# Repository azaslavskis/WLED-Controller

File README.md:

# WLED Controller ⚡

A compact ESP32-C3 based controller board for running addressable LED strips with **WLED** and integrating them into **Home Assistant**.

---

## What this project includes

- **Hardware design files** (KiCad project, production outputs, 3D model assets)
- **Firmware patch helper** for building a patched WLED version
- **Assembly references** for the current controller revision

---

## ⚠️ Current hardware status

> **Do not order this PCB revision yet** — the board still has known issues.

### Known issues to fix before ordering

1. `R7` / `EN` pin of `XL1509-5.0V` should be connected to **GND**, not input.
2. ESP32-C3 **pin 9** must be pulled correctly for reliable boot.
3. `DS18B20` pin must be pulled to **3.3V** (fixed on rev **1.6**).
4. More physical spacing is needed for `C1`, `C3`, and `C9`.

---

## Assembled unit

---

## Build patched firmware

Run the helper script directly:

```bash
wget https://raw.githubusercontent.com/azaslavskis/WLED-Controller/refs/heads/main/software/WLED-Git_patch/patch.sh \
  && chmod +x patch.sh \
  && ./patch.sh
```

---

## Repository layout (high level)

- `hardware/` → PCB project, exports, and fabrication artifacts
- `software/` → firmware patching/build helper files
- `3d-models/` → enclosure and mounting models

---

## Project goal

Create a reliable, DIY-friendly LED controller that is easy to deploy in smart-home setups and flexible enough for custom lighting projects.

## Rework is comming soon

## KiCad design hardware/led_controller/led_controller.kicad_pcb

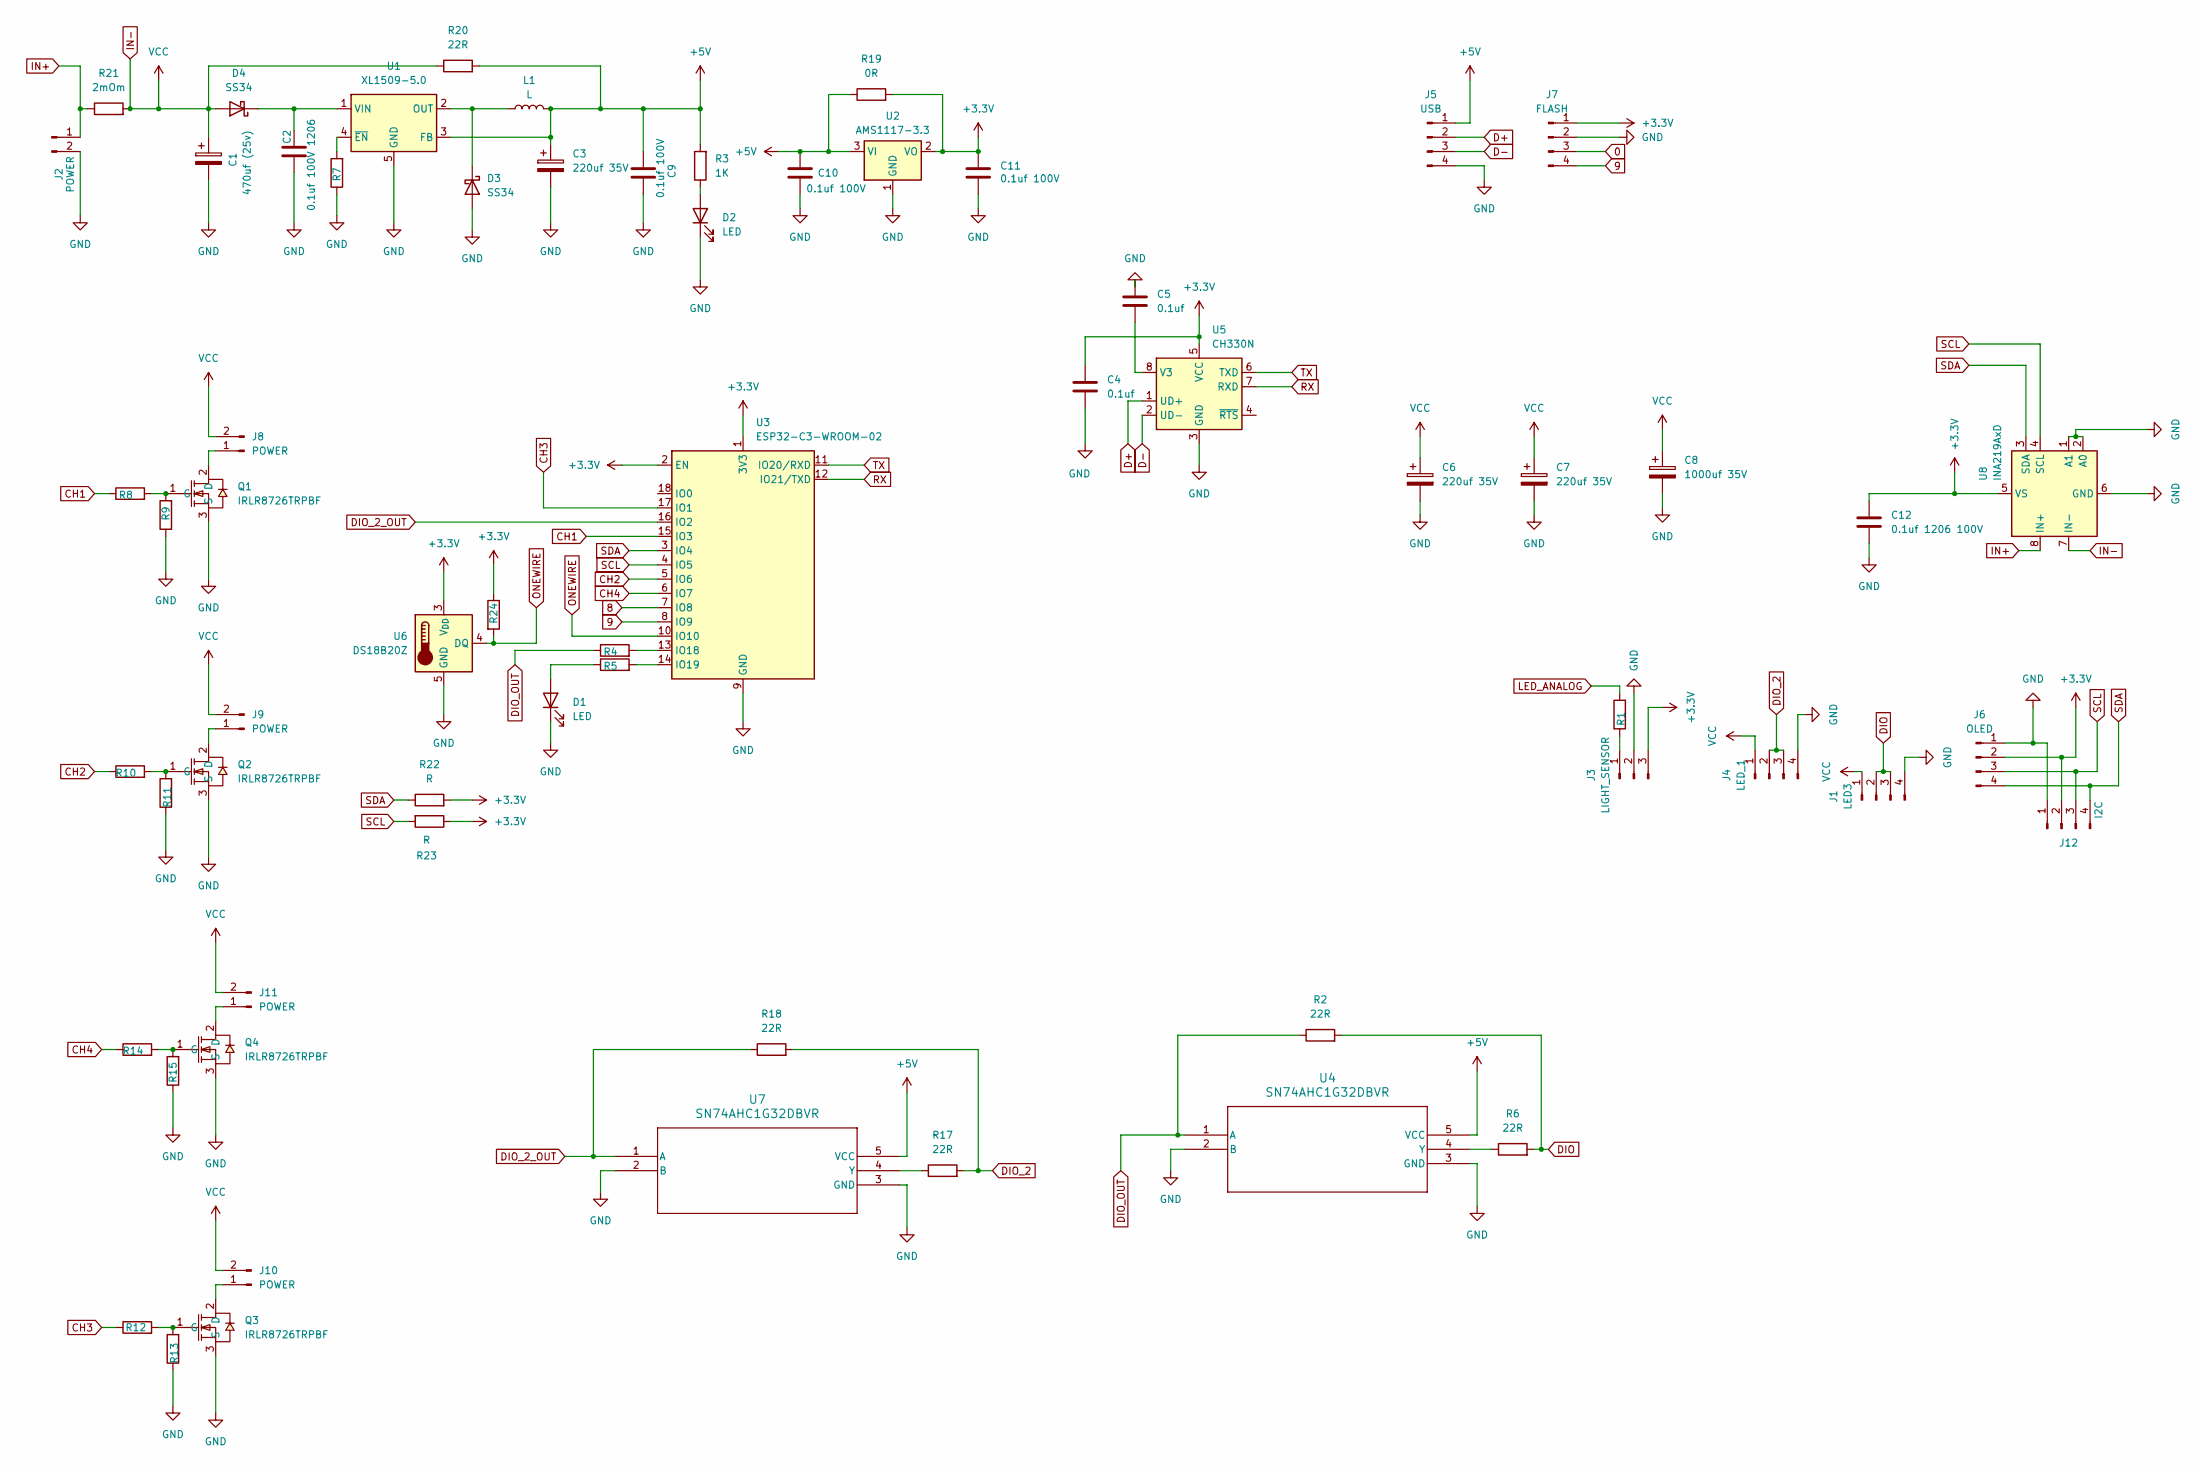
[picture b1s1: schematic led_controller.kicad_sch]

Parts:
C1: 470uf (25v); CP_Radial_D7.5mm_P2.50mm
C2: 0.1uf 100V 1206; C_1206_3216Metric
C3: 220uf 35V; CP_Radial_D7.5mm_P2.50mm
C4, C5: 0.1uf; C_1206_3216Metric
C6, C7: 220uf 35V; CP_Radial_D5.0mm_P2.50mm
C8: 1000uf 35V; CP_Radial_D7.5mm_P2.50mm
C9, C10, C11: 0.1uf 100V; C_1206_3216Metric
C12: 0.1uf 1206 100V; R_1206_3216Metric
D1, D2: LED; LED_1206_3216Metric
D3, D4: SS34; D_SMA
J1: LED3; JST_XH_B4B-XH-AM_1x04_P2.50mm_Vertical
J2, J8, J9, J10, J11: POWER; PhoenixContact_MC_1,5_2-G-5.08_1x02_P5.08mm_Horizontal
J3: LIGHT_SENSOR; PinHeader_1x03_P2.54mm_Vertical
J4: LED_1; JST_XH_B4B-XH-AM_1x04_P2.50mm_Vertical
J5: USB; JST_XH_B4B-XH-AM_1x04_P2.50mm_Vertical
J6: OLED; PinHeader_1x04_P2.54mm_Vertical
J7: FLASH; PinHeader_1x04_P2.54mm_Vertical
J12: I2C; JST_XH_B4B-XH-AM_1x04_P2.50mm_Vertical
L1: L; L_Coilcraft_XAL8050-223
Q1, Q2, Q3, Q4: IRLR8726TRPBF; TO-252-2_L6.6-W6.1-P4.58-LS9.9-TL; LCSC Part C81137
R1, R2, R4, R6, R7, R15, R17, R18, R20: 22R; R_1206_3216Metric
R3: 1K; R_1206_3216Metric
R5, R8, R10, R12, R14: 220R; R_1206_3216Metric
R9, R11, R13, R24: 10K; R_1206_3216Metric
R19: 0R; R_1206_3216Metric
R21: 2mOm; R_2512_6332Metric
R22, R23: R; R_1206_3216Metric
U1: XL1509-5.0; SOIC-8_3.9x4.9mm_P1.27mm
U2: AMS1117-3.3; SOT-223-3_TabPin2
U3: ESP32-C3-WROOM-02; ESP32-C3-WROOM-02U
U4, U7: SN74AHC1G32DBVR; DBV5
U5: CH330N; SOIC-8_3.9x4.9mm_P1.27mm
U6: DS18B20Z; SOIC-8_3.9x4.9mm_P1.27mm
U8: INA219AxD; SOIC-8_3.9x4.9mm_P1.27mm

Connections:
0: J7.3, U3.18 (IO0)
+3.3V: C4.1, C11.1, C12.2, J3.3, J6.2, J7.1, J12.2, R19.2, R22.2, R23.1, R24.1, U2.2 (VO), U3.1 (3V3), U3.2 (EN), U5.5 (VCC), U6.3 (V_{DD}), U8.5 (VS)
+5V: C3.1, C9.1, C10.1, J5.1, L1.2, R3.2, R19.1, R20.2, U1.3 (FB), U2.3 (VI), U4.5 (VCC), U7.5 (VCC)
CH1: R8.1, U3.15 (IO3)
CH2: R10.1, U3.5 (IO6)
CH4: R14.1, U3.6 (IO7)
D+: J5.2, U5.1 (UD+)
D-: J5.3, U5.2 (UD-)
DIO: J1.2, J1.3, R2.2, R6.2
DIO_2: J4.2, J4.3, R17.2, R18.2
DIO_2_OUT: R18.1, U3.16 (IO2), U7.1 (A)
DIO_OUT: R2.1, R4.1, U4.1 (A)
GND: C1.2, C2.2, C3.2, C4.2, C5.1, C6.2, C7.2, C8.2, C9.2, C10.2, C11.2, C12.1, D1.1 (K), D2.1 (K), D3.2 (A), J1.4, J2.2, J3.2, J4.4, J5.4, J6.1, J7.2, J12.1, Q1.3 (S), Q2.3 (S), Q3.3 (S), Q4.3 (S), R7.1, R9.1, R11.1, R13.1, R15.1, U1.5 (GND), U1.6 (GND), U1.7 (GND), U1.8 (GND), U2.1 (GND), U3.9 (GND), U3.19 (GND), U4.2 (B), U4.3 (GND), U5.3 (GND), U6.5 (GND), U7.2 (B), U7.3 (GND), U8.1 (A1), U8.2 (A0), U8.6 (GND)
IN+: J2.1, R21.1, U8.8 (IN+)
IN-: C1.1, C6.1, C7.1, C8.1, D4.2 (A), J1.1, J4.1, J8.2, J9.2, J10.2, J11.2, R20.1, R21.2, U8.7 (IN-)
unnamed: D1.2 (A), R5.1
unnamed: D2.2 (A), R3.1
unnamed: D3.1 (K), L1.1, U1.2 (OUT)
unnamed: C2.1, D4.1 (K), U1.1 (VIN)
unnamed: J3.1, R1.1
unnamed: J8.1, Q1.2 (D)
unnamed: J9.1, Q2.2 (D)
unnamed: J10.1, Q3.2 (D)
unnamed: J11.1, Q4.2 (D)
unnamed: Q1.1 (G), R8.2, R9.2
unnamed: Q2.1 (G), R10.2, R11.2
unnamed: Q3.1 (G), R12.2, R13.2
unnamed: Q4.1 (G), R14.2, R15.2
unnamed: R7.2, U1.4 (~EN)
unnamed: R4.2, U3.13 (IO18)
unnamed: R5.2, U3.14 (IO19)
unnamed: R6.1, U4.4 (Y)
unnamed: C5.2, U5.8 (V3)
unnamed: R17.1, U7.4 (Y)
ONEWIRE: R24.2, U3.10 (IO10), U6.4 (DQ)
RX: U3.12 (IO21/TXD), U5.7 (RXD)
SCL: J6.3, J12.3, R23.2, U3.4 (IO5), U8.4 (SCL)
SDA: J6.4, J12.4, R22.1, U3.3 (IO4), U8.3 (SDA)
TX: U3.11 (IO20/RXD), U5.6 (TXD)

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
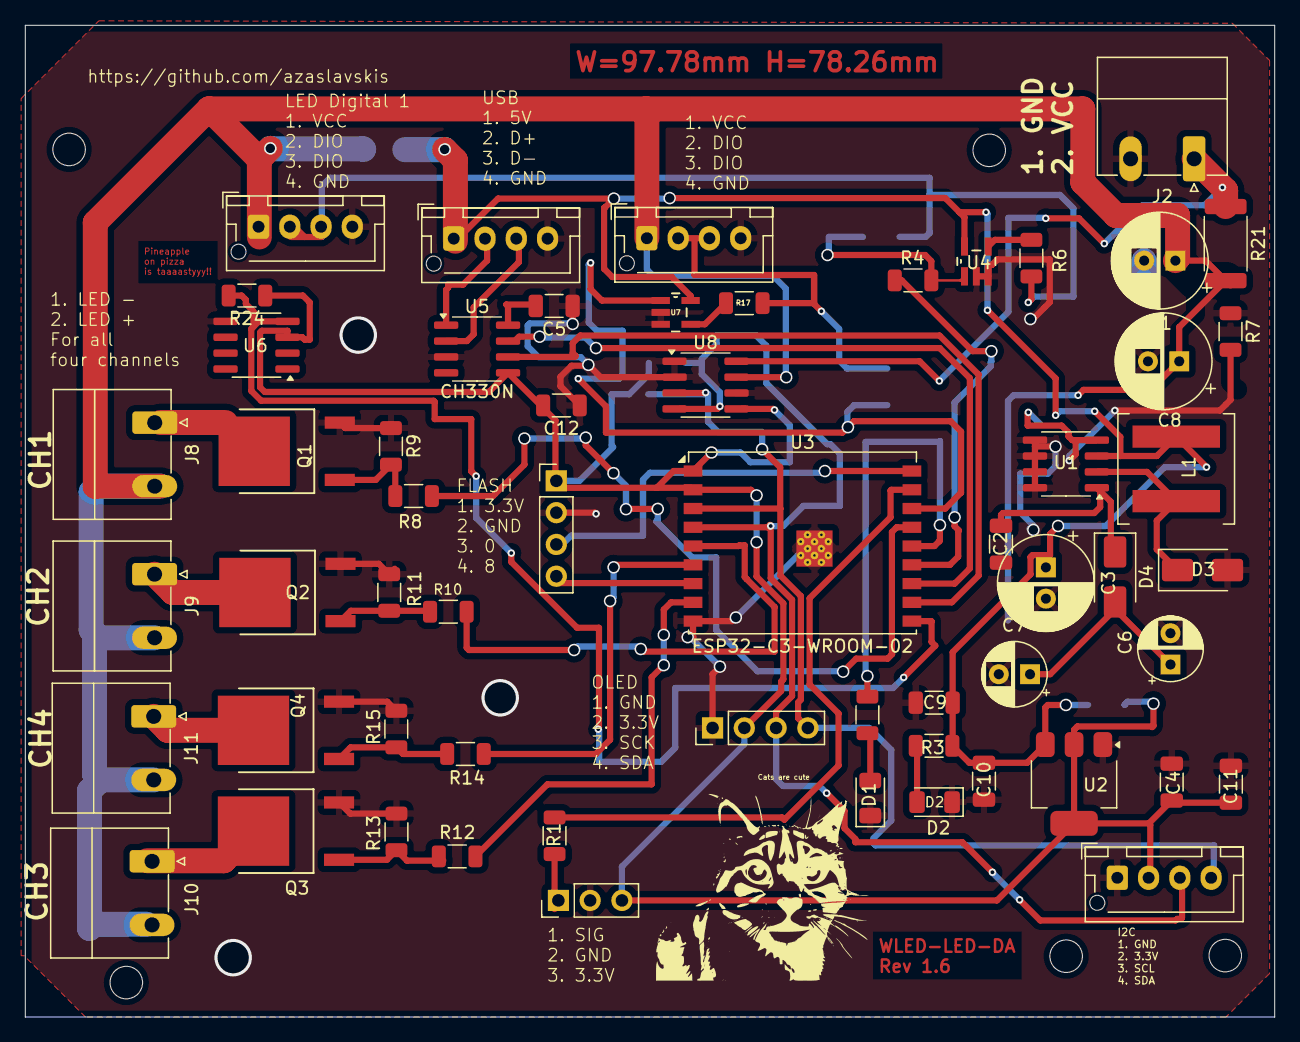
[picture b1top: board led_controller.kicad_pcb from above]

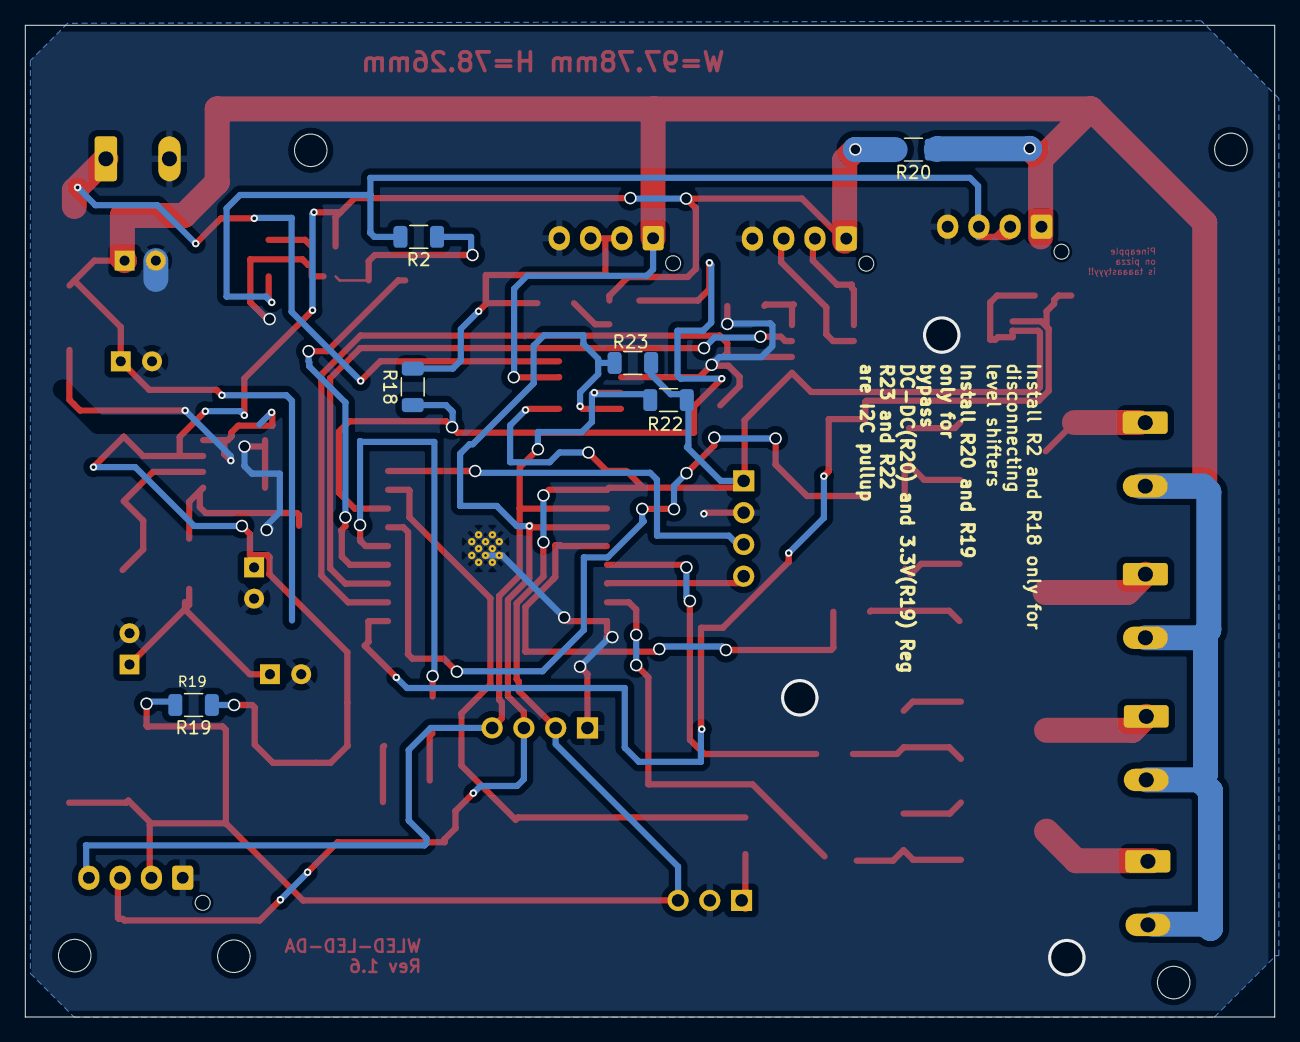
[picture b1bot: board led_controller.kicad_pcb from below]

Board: 2 copper layers, 99.9 x 79.3 mm, 64 parts (6 on the bottom side), 42 nets.

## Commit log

2024-12-02 append and PCB boards design
2024-12-14 add demo software sketch
2024-12-14 added WLED software fork
2024-12-14 added last pcb verison
2024-12-14 added pcb issues log README.md
2024-12-15 uploading stuff finally
2024-12-15 added wled patch file
2024-12-15 added only patch file. the instructions coming soon
2024-12-15 add 3d parts
2024-12-15 controller
2024-12-17 appended last version of controller case
2024-12-18 add link for patch
2026-03-18 Rewrite README with structured project overview
2026-03-18 Update README title by removing an emoji
    Removed emoji from the project title in README.
